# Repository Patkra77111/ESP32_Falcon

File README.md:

# ESP32_Falcon
Jest to customowa płytka deweloperska oparta na module ESP32-S3, była ona inspirowana designem STM32 Nucleo. Jest to projekt rekrutacyjny do koła naukowego FALCON na Politechnice Wrocławskiej. Został on całkowicie wykonany w KiCad.

## Specyfikacja
**Mikrokontroler:** ESP32-S3-WROOM-1.
* **Komunikacja i Zasilanie:** Złącze USB-C z układem zabezpieczającym ESD.
* **Czujniki:** Zintegrowany czujnik IMU BMI270 podłączony przez I2C.
* **Rozszerzalność:** Wyprowadzenia sygnałowe na złączach goldpin w układzie Nucleo.

### 1. Schemat 

### 2. Layout PCB

### 3. Model 3D

## Główne Decyzje Projektowe i Zasady EMC
1. **Prowadzenie sygnałów USB (D+/D-):** Linie danych z USB-C zostały poprowadzone jako para różnicowa na jednej warstwie, bez użycia przelotek, w celu zachowania spójności impedancji.
2. **Zachowanie strefy Keepout dla anteny:** Moduł ESP32-S3 został umieszczony na krawędzi płytki, a jego antena znajduje się całkowicie poza obrysem miedzi i laminatu, aby uniknąć tłumienia sygnału.
3. **Dystrybucja Zasilania i Decoupling:** Ścieżki zasilające mają odpowiednią grubość (0.4mm - 0.5mm) i są prowadzone bezpośrednio do głównych odbiorników. Kondensatory filtrujące zostały umieszczone w bezpośrednim sąsiedztwie pinów zasilających ESP32 oraz BMI270.
4. **Wylewki GND (Copper Pours):** Wylewki masy na obu stronach laminatu. Połacie masy zostały połączone za pomocą przelotek.

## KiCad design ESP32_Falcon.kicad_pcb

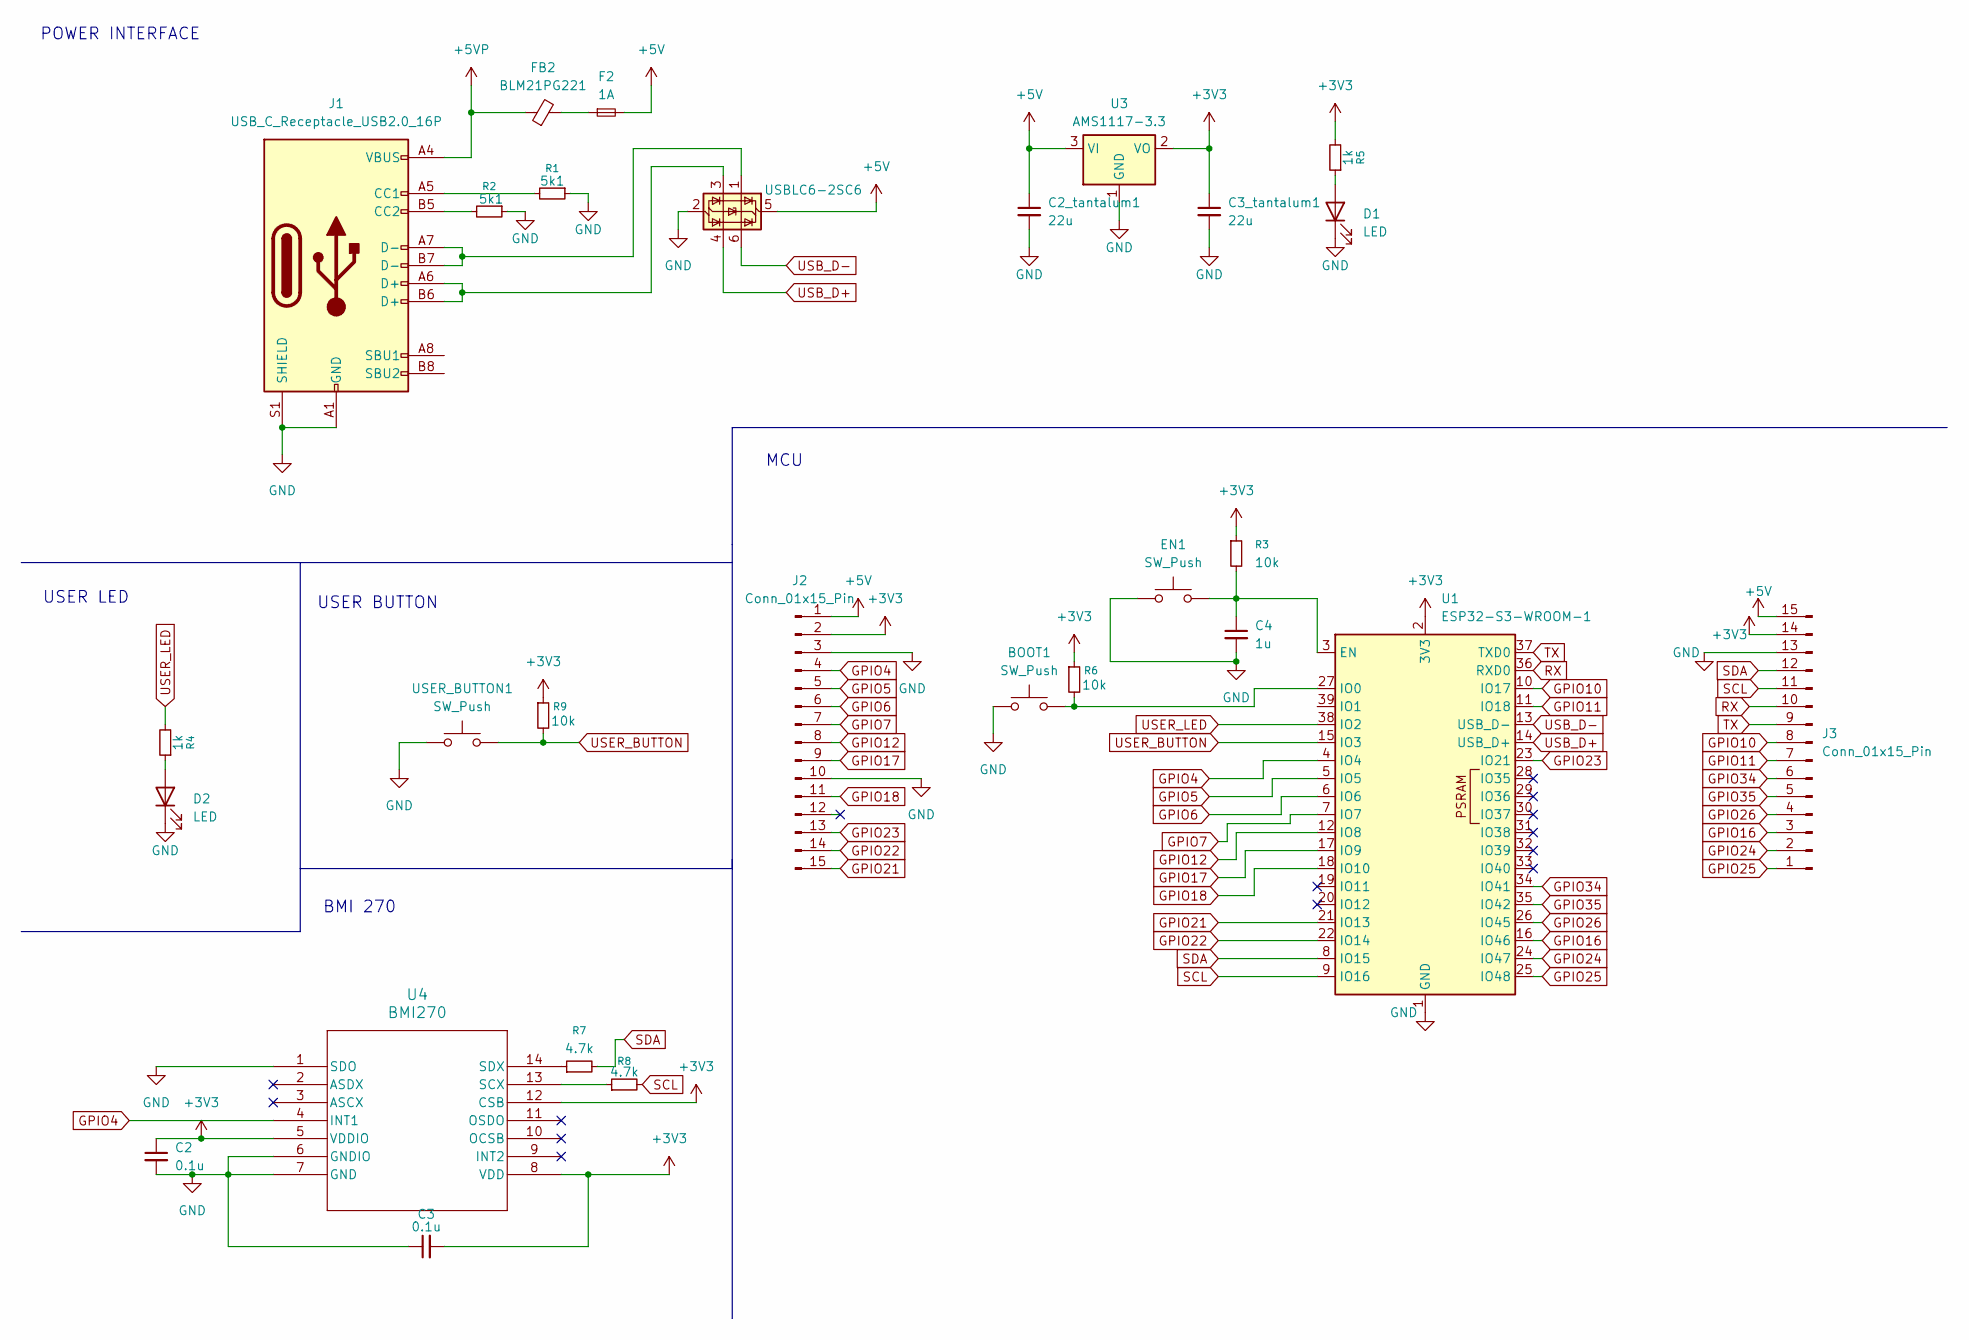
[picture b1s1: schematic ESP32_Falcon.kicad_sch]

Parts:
BOOT1: SW_Push; SW_Push_1TS009xxxx-xxxx-xxxx_6x6x5mm
C2, C3: 0.1u; C_0805_2012Metric_Pad1.18x1.45mm_HandSolder
C2_tantalum1, C3_tantalum1: 22u; C_0805_2012Metric_Pad1.18x1.45mm_HandSolder
C4: 1u; C_0805_2012Metric_Pad1.18x1.45mm_HandSolder
D1, D2: LED; LED_0805_2012Metric_Pad1.15x1.40mm_HandSolder
EN1: SW_Push; SW_Push_1TS009xxxx-xxxx-xxxx_6x6x5mm
F2: 1A; Fuse_1206_3216Metric_Pad1.42x1.75mm_HandSolder
FB2: BLM21PG221; L_0805_2012Metric_Pad1.05x1.20mm_HandSolder
J1: USB_C_Receptacle_USB2.0_16P; USB_C_Receptacle_XKB_U262-16XN-4BVC11
J2, J3: Conn_01x15_Pin; PinHeader_1x15_P2.54mm_Vertical
R1, R2: 5k1; R_0805_2012Metric_Pad1.20x1.40mm_HandSolder
R3, R6, R9: 10k; R_0805_2012Metric_Pad1.20x1.40mm_HandSolder
R4, R5: 1k; R_0805_2012Metric_Pad1.20x1.40mm_HandSolder
R7, R8: 4.7k; R_0805_2012Metric_Pad1.20x1.40mm_HandSolder
U1: ESP32-S3-WROOM-1
U2: USBLC6-2SC6; SOT-23-6
U3: AMS1117-3.3; SOT-223-3_TabPin2
U4: BMI270; BMI270_BOS
USER_BUTTON1: SW_Push; SW_Push_1TS009xxxx-xxxx-xxxx_6x6x5mm

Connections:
+3V3: C2.1, C3.2, C3_tantalum1.1, J2.2, J3.14, R3.1, R5.2, R6.1, R9.1, U1.2 (3V3), U3.2 (VO), U4.5 (VDDIO), U4.8 (VDD), U4.12 (CSB); also elsewhere on the board
+5V: C2_tantalum1.1, F2.2, J2.1, J3.15, U2.5 (VBUS), U3.3 (VI); also elsewhere on the board
+5VP: FB2.1, J1.A4 (VBUS), J1.A9 (VBUS), J1.B4 (VBUS), J1.B9 (VBUS)
GND: BOOT1.1, C2.2, C2_tantalum1.2, C3.1, C3_tantalum1.2, C4.2, D1.1 (K), D2.1 (K), EN1.1, J1.A1 (GND), J1.A12 (GND), J1.B1 (GND), J1.B12 (GND), J1.S1 (SHIELD), J2.3, J2.10, J3.13, R1.1, R2.1, U1.1 (GND), U1.40 (GND), U1.41 (GND), U2.2 (GND), U3.1 (GND), U4.1 (SDO), U4.6 (GNDIO), U4.7 (GND), USER_BUTTON1.1; also elsewhere on the board
GPIO4: J2.4, U1.4 (IO4), U4.4 (INT1)
GPIO5: J2.5, U1.5 (IO5)
GPIO6: J2.6, U1.6 (IO6)
GPIO7: J2.7, U1.7 (IO7)
GPIO10: J3.8, U1.10 (IO17)
GPIO11: J3.7, U1.11 (IO18)
GPIO12: J2.8, U1.12 (IO8)
GPIO16: J3.3, U1.16 (IO46)
GPIO17: J2.9, U1.17 (IO9)
GPIO18: J2.11, U1.18 (IO10)
GPIO21: J2.15, U1.21 (IO13)
GPIO22: J2.14, U1.22 (IO14)
GPIO23: J2.13, U1.23 (IO21)
GPIO24: J3.2, U1.24 (IO47)
GPIO25: J3.1, U1.25 (IO48)
GPIO26: J3.4, U1.26 (IO45)
GPIO34: J3.6, U1.34 (IO41)
GPIO35: J3.5, U1.35 (IO42)
unnamed: D1.2 (A), R5.1
unnamed: D2.2 (A), R4.1
unnamed: F2.1, FB2.2
unnamed: J1.A5 (CC1), R1.2
unnamed: J1.B5 (CC2), R2.2
unnamed: J1.A6 (D+), J1.B6 (D+), U2.3 (I/O2)
unnamed: J1.A7 (D-), J1.B7 (D-), U2.1 (I/O1)
unnamed: C4.1, EN1.2, R3.2, U1.3 (EN)
unnamed: BOOT1.2, R6.2, U1.27 (IO0)
unnamed: R8.1, U4.13 (SCX)
unnamed: R7.1, U4.14 (SDX)
RX: J3.10, U1.36 (RXD0)
SCL: J3.11, R8.2, U1.9 (IO16)
SDA: J3.12, R7.2, U1.8 (IO15)
TX: J3.9, U1.37 (TXD0)
USB_D+: U1.14 (USB_D+), U2.4 (I/O2)
USB_D-: U1.13 (USB_D-), U2.6 (I/O1)
USER_BUTTON: R9.2, U1.15 (IO3), USER_BUTTON1.2
USER_LED: R4.2, U1.38 (IO2)

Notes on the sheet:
BMI 270
USER LED
MCU
POWER INTERFACE
USER BUTTON

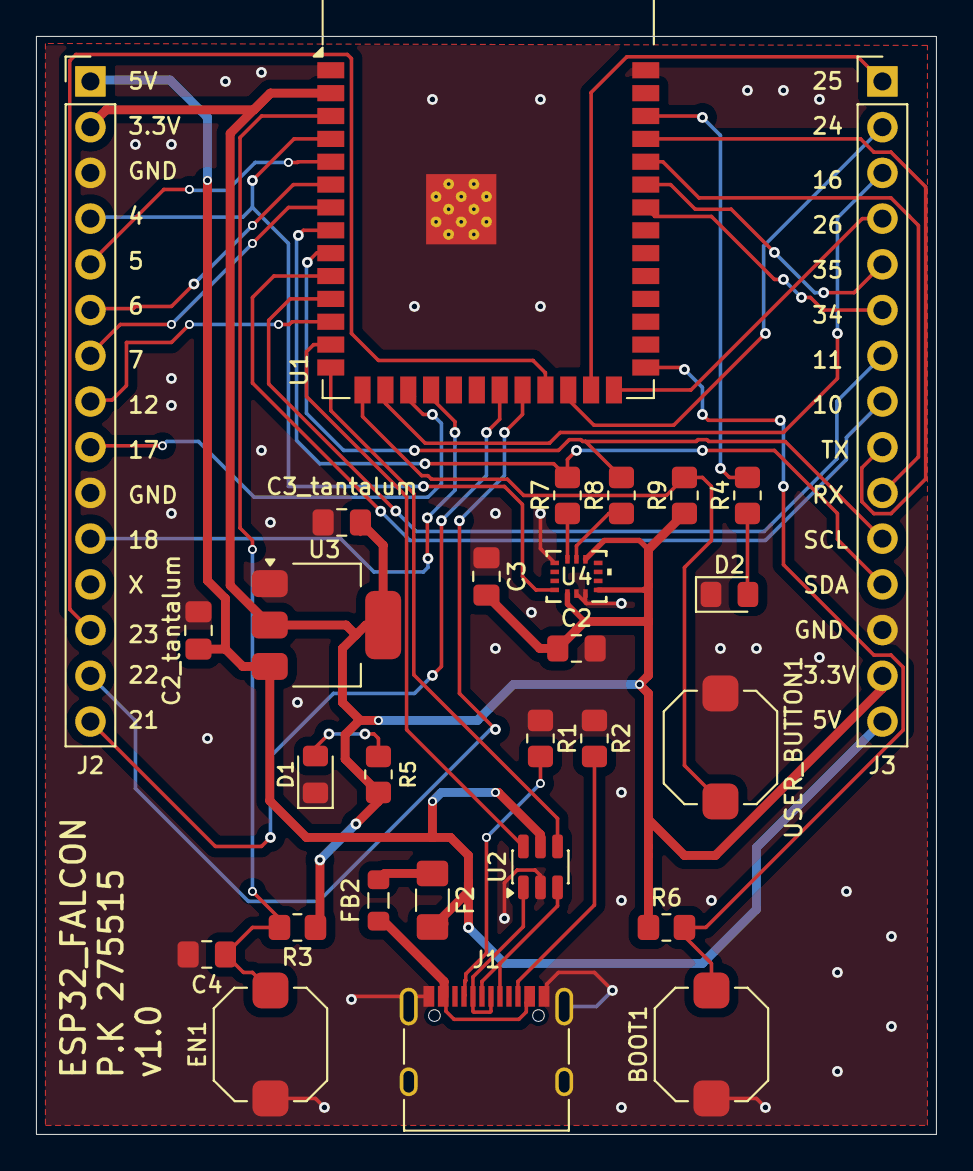
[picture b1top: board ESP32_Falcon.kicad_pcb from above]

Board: 2 copper layers, 50.0 x 61.0 mm, 28 parts (0 on the bottom side), 41 nets.

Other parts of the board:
C2_tantalum, C3_tantalum: 22u; C_0805_2012Metric_Pad1.18x1.45mm_HandSolder

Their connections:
+3V3: C3_tantalum.1; also elsewhere on the board
+5V: C2_tantalum.1; also elsewhere on the board
GND: C2_tantalum.2, C3_tantalum.2; also elsewhere on the board

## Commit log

2026-03-28 Początek projektu, rozpoczęcie sekcji zasilania
2026-03-31 Praktycznie skonczony schematic
2026-03-31 Poczatek PCB
2026-04-01 Podlaczone glowne sciezki
2026-04-02 skończony projekt
2026-04-02 Rename ESP32_Falcon.csv to ESP32_Falcon_BOM.csv
